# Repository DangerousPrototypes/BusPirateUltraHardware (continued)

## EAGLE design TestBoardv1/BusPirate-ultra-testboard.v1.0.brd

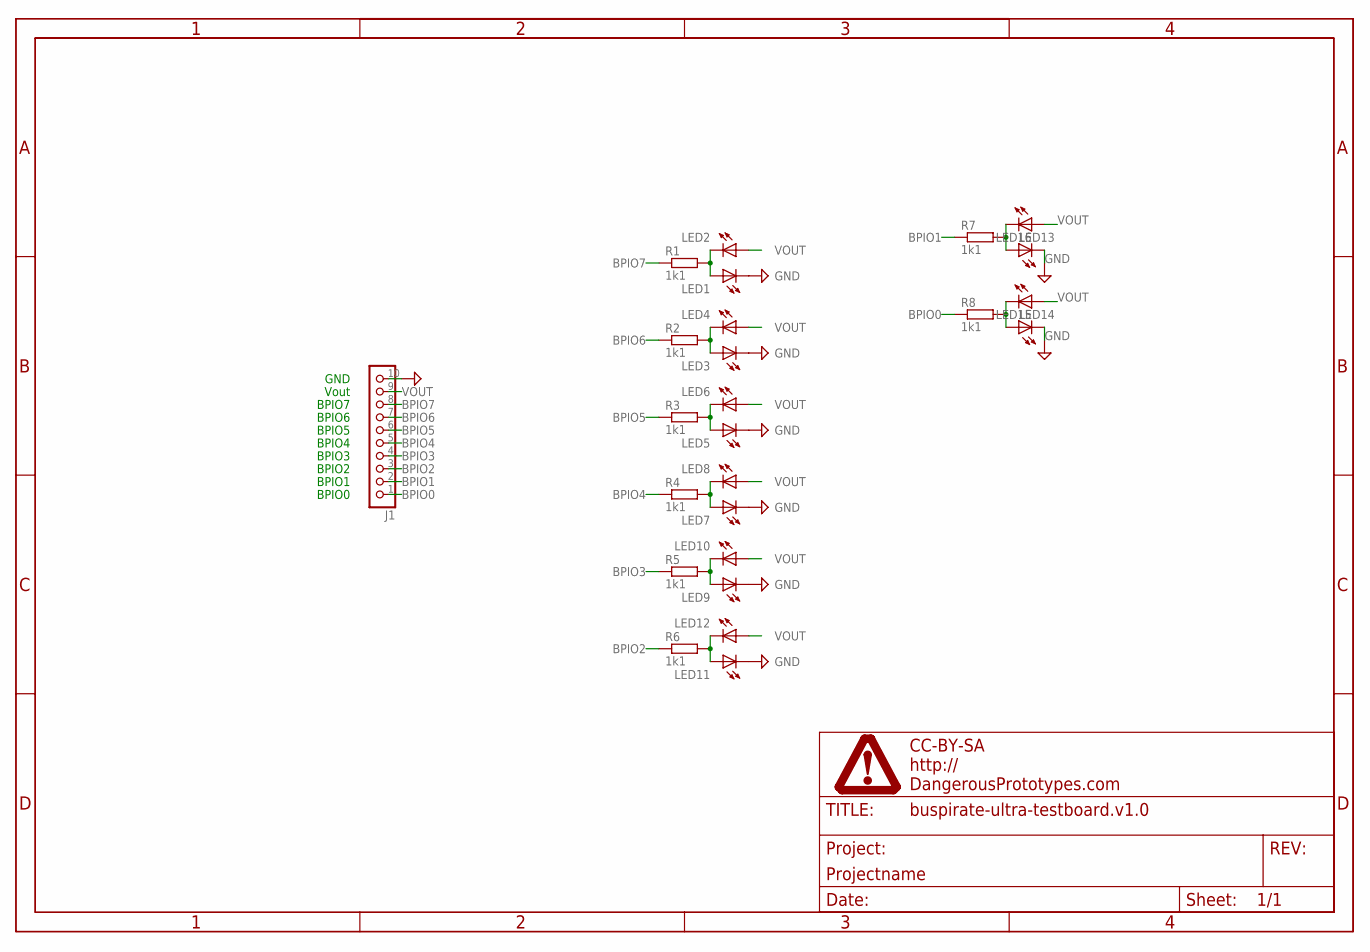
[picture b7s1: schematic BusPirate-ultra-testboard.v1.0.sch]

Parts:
J1: CON_HEADER_1X10-RIGHT_ANGLED_PTH; M1X10_FEMALE_RIGHT_ANGLED_PTH
LED1, LED2, LED3, LED4, LED5, LED6, LED7, LED8, LED9, LED10, LED11, LED12, LED13, LED14, LED15, LED16: LED-0805; LED-805
PAGE1: FRAME_DINA4_L; DP_LOGO
R1, R2, R3, R4, R5, R6, R7, R8: 1k1; R603

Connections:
BPIO0: J1.1, R8.1
BPIO1: J1.2, R7.1
BPIO2: J1.3, R6.1
BPIO3: J1.4, R5.1
BPIO4: J1.5, R4.1
BPIO5: J1.6, R3.1
BPIO6: J1.7, R2.1
BPIO7: J1.8, R1.1
GND: J1.10, LED1.C, LED3.C, LED5.C, LED7.C, LED9.C, LED11.C, LED13.C, LED14.C
unnamed: LED1.A, LED2.C, R1.2
unnamed: LED3.A, LED4.C, R2.2
unnamed: LED5.A, LED6.C, R3.2
unnamed: LED7.A, LED8.C, R4.2
unnamed: LED9.A, LED10.C, R5.2
unnamed: LED11.A, LED12.C, R6.2
unnamed: LED14.A, LED15.C, R8.2
unnamed: LED13.A, LED16.C, R7.2
VOUT: J1.9, LED2.A, LED4.A, LED6.A, LED8.A, LED10.A, LED12.A, LED15.A, LED16.A

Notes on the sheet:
BPIO0
Vout
BPIO7
BPIO6
BPIO5
BPIO4
BPIO3
BPIO2
BPIO1
GND

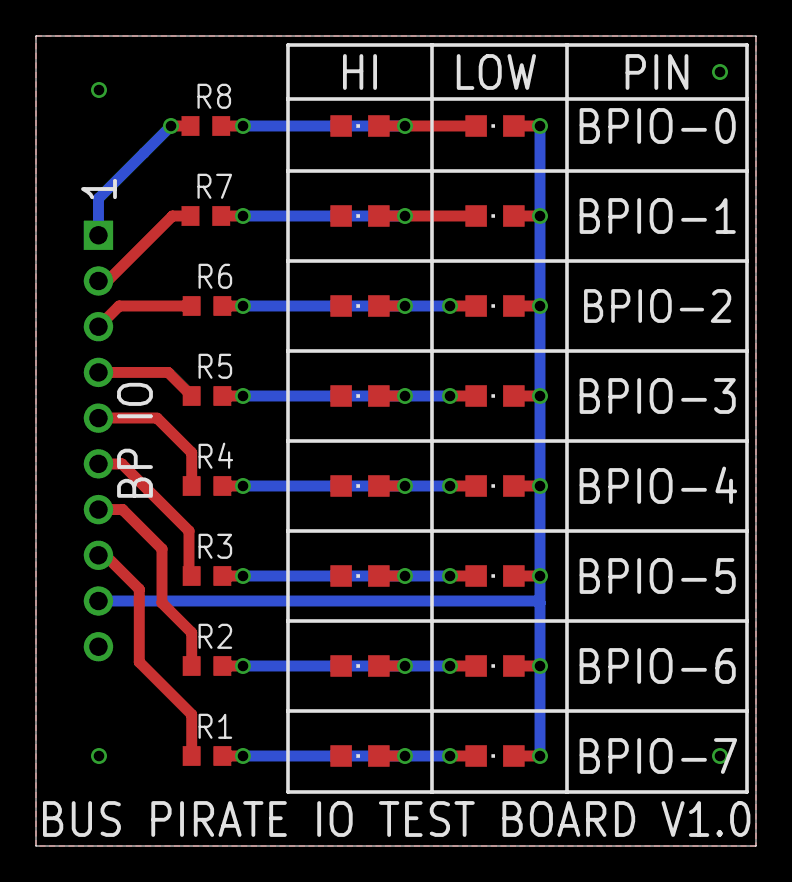
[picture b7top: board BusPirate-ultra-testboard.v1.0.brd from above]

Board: 2 copper layers, 40.0 x 45.0 mm, 26 parts (1 on the bottom side), 18 nets.

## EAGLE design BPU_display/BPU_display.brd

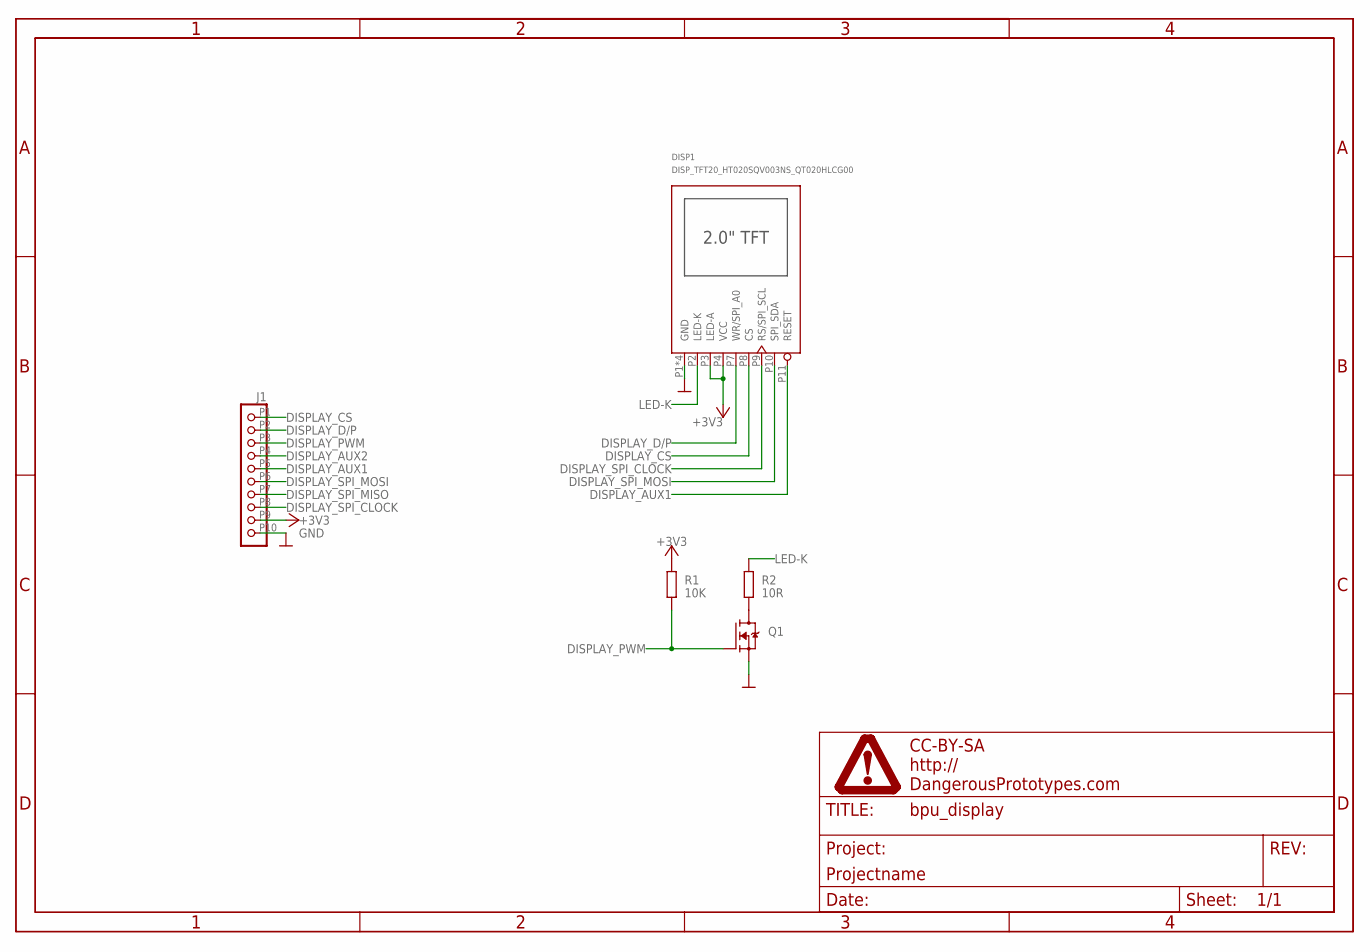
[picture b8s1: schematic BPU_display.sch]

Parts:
DISP1: DISP_TFT20_HT020SQV003NS_QT020HLCG00; HT020SQV003NS_QT020HLCG00
J1: CON_MOLEX_MALE_SMT_RIGHT_ANGLE_1.25; MOLEX_532611071
PAGE1: FRAME_DINA4_L; DP_LOGO
Q1: TRANSISTOR_FET_BS170-SOT-23; SOT-23
R1: 10K; R0603
R2: 10R; R0603

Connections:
+3V3: DISP1.P3 (LED-A), DISP1.P4 (VCC), J1.P9 (9), R1.2
DISPLAY_AUX1: DISP1.P11 (RESET), J1.P5 (5)
DISPLAY_AUX2: J1.P4 (4)
DISPLAY_CS: DISP1.P8 (CS), J1.P1 (1)
DISPLAY_D/P: DISP1.P7 (WR/SPI_A0), J1.P2 (2)
DISPLAY_PWM: J1.P3 (3), Q1.1 (G), R1.1
DISPLAY_SPI_CLOCK: DISP1.P9 (RS/SPI_SCL), J1.P8 (8)
DISPLAY_SPI_MISO: J1.P7 (7)
DISPLAY_SPI_MOSI: DISP1.P10 (SPI_SDA), J1.P6 (6)
GND: DISP1.P1 (GND), DISP1.P5 (GND), DISP1.P6 (GND), DISP1.P12 (GND), J1.P10 (10), Q1.2 (S)
LED-K: DISP1.P2 (LED-K), R2.2
unnamed: Q1.3 (D), R2.1

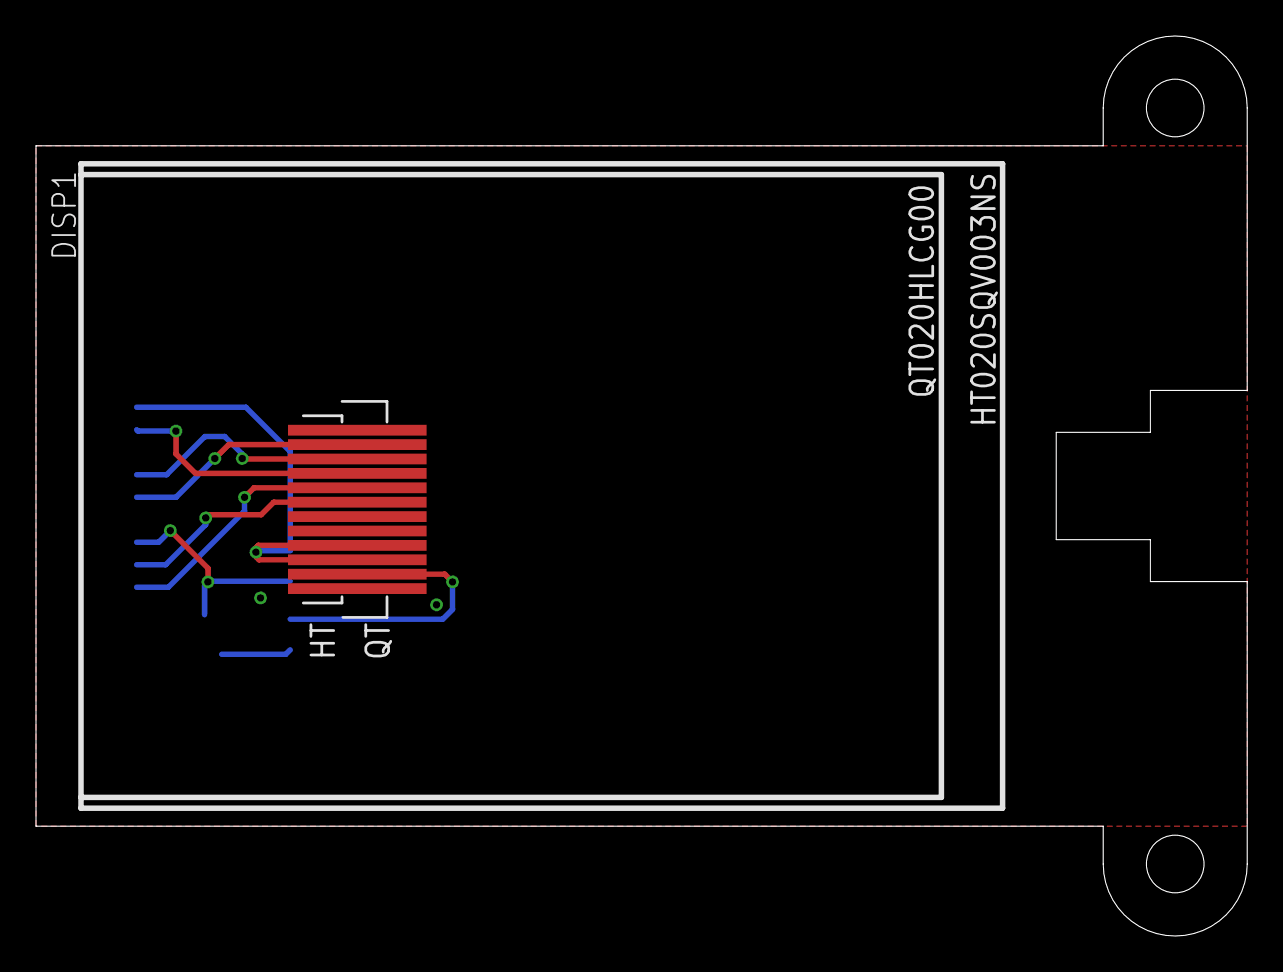
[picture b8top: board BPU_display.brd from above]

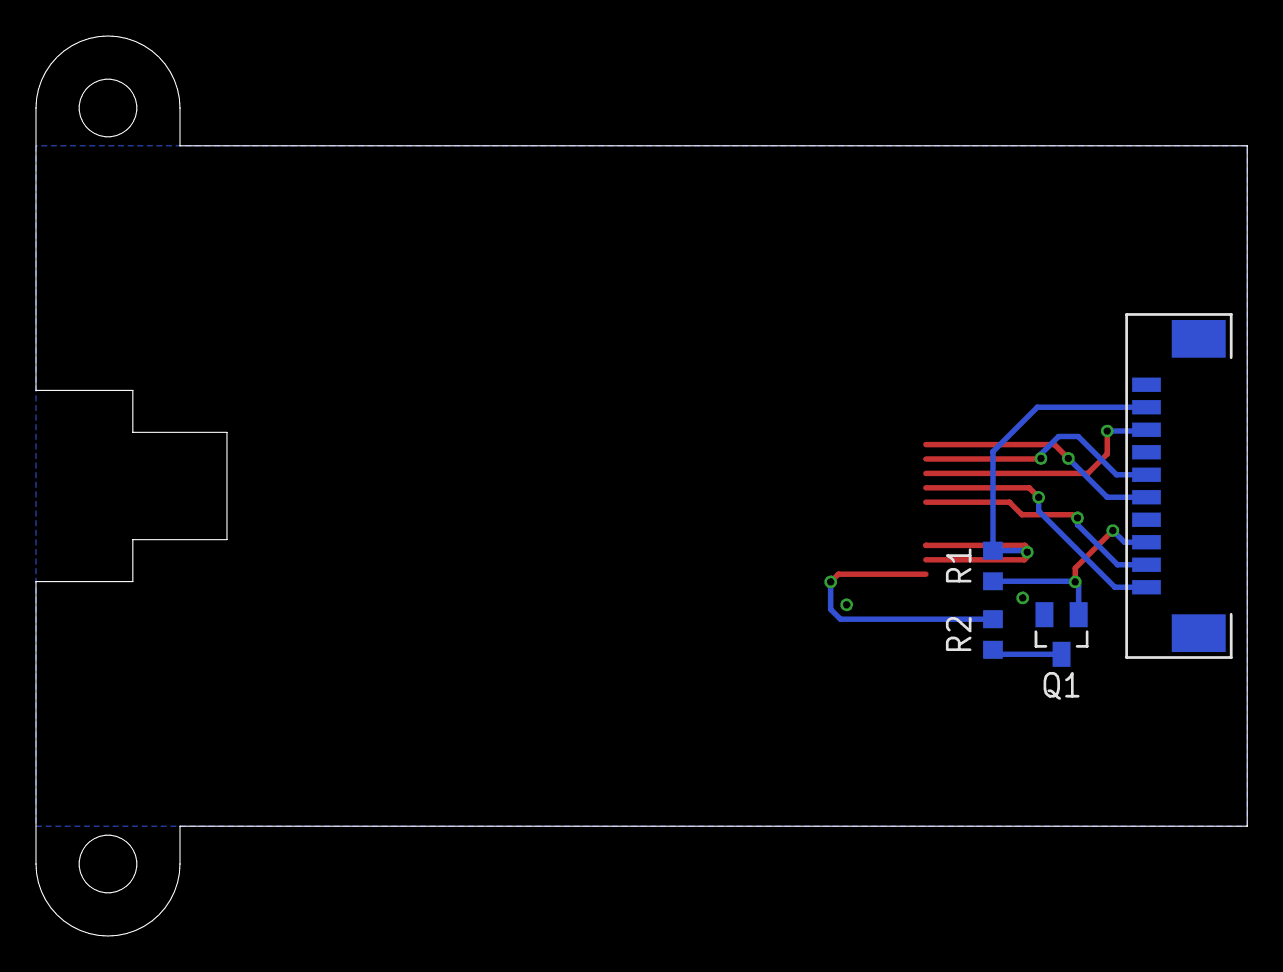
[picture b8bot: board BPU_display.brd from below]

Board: 2 copper layers, 67.3 x 50.0 mm, 6 parts (4 on the bottom side), 10 nets.

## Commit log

2019-08-26 initial check in from old repo https://github.com/DangerousPrototypes/Bus_Pirate_Ultra
2019-08-26 spreadsheets for calculating margining on the Vreg
2019-08-28 continue routing
2019-08-28 routed power traces
2019-08-29 board routing done, add usbc bottom PTH chassis mount library
2019-08-30 creted gerber for v1b
2019-09-06 added BP 'sail' daughter board
2019-09-06 make IO connector protrusion clearance to 1.5mm
2019-09-06 add DWG reference
2019-09-10 added vout and GND test point. add LED status to vout
2019-09-10 created geber for BPU display
2019-09-11 fix testboard IO header to match v1b, created gerbers
2019-09-24 new BPUltra.v.1.0C revision broke RN3 to individual 10K R603 resistors Added 1uF 0603 cap to U14 connect OE and DIR of latch (245) to FPGA Change values of the following parts: R27 to 100K R32 to 10K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
2019-10-03 fix bom parts naming change back to original SC-70-5 and SC-70-6 footprints for 74LVC1G07DBV and SN74LVC1T45DBV added decoupling caps for open drain buffers(on going)
2019-10-04 Revert previous commit to v1b, wrong version commited. changes should be on v1c not v1b.
    This reverts commit d10a26b079303959180bb4ab2616075854f9b9d1.
2019-10-05 new BPUltra.v.1.0C revision removed some text labels renamed BPIO pin labels fix bom parts naming change back to original SC-70-5 and SC-70-6 footprints for 74LVC1G07DBV and SN74LVC1T45DBV added deco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
2019-10-05 re-number parts logically changed C302 to 1uF add 4.7uF input cap on VR1 add 4.7uF input cap on VR2 add RC filter 25R and 1.5nF on ADC MUX buffer
2019-10-10 added ADC ADS7041 and wired to FPGA pin 45, 47 and 48 changed 3.3V regulator to bigger MCP1700 changed mux to 16-bit version 74HCT4067, added one new address line S3 to FPGA (not connected yet) conne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
2019-10-10 change supply of ADC chip to 3.3V
2019-10-15 updates on v1c schematic moved MCU_VPU to PA9, free up A10 moved DISPLAY_CS to PF11 (former DISPLAY_D/P) and DISPLAY_D/P to PB1, free up A6 moved FPGA MCU_INT1 from GBIN5 to FPGA pin 115 wired PG8 to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
2019-10-15 renamed DISPLAY_AUX2 to DISPLAY_AUX1 connected to PB1 renamed DISPLAY_AUX1 to DISPLAY_RESET and connected to PB2/BOOT1, wired a pull down resistor too rewired DISPLAY_CS from PF11 to PC4 rewired DISP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
2019-10-15 rewiring of v1c schematic continues
    renamed MCU_AUX7 to MCU_INT0
    renamed MCU_AUX8 to MCU_INT1
    renamed MCU_INT0 to MCU_PWM0
    renamed PWM to MCU_PWM1
    moved LAT_OE to FPGA pin 96
    moved LAT_DIR to FPGA pin 95
2019-10-16 continued on v1c schematic changes renamed MCU_AUX4 to MCU_INT3 and move it from MCU PD6 to PD2 renamed MCU_INT1I to MCU_AUX0 fix display connections
2019-10-16 continue on v1c schematic revisions -removed net DISPLAY_CSI on MCU pin 49 -renamed MCU_AUX5 to MCU_AUX4 and MCU_AUX6 to MCU_AUX5 -renamed MCU_ADC5 to MCU_ADC2 -renamed MCU_ADC6 to MCU_ADC3 -wired MC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
2019-10-20 finishing up routing on v1c board
2019-10-22 change display connector to FPC connector, done routing
2019-11-02 update reference dwg
2019-12-14 display board, fonts, 25lc eeprom breakout test board
2019-12-14 display board reorganization.
2020-04-21 preliminary commit of Bus Pirate Ultra v2, additional designs attribute to ULX3s https://github.com/emard/ulx3s and Butterstick https://github.com/gregdavill/ButterStick
2020-06-01 added 3d model of bus pirate ultra v1 case in freecad
2021-04-13 Added boxy corner version of the case on v1.1
2021-04-14 added v1.2 case, revert usb port back to rounded corner hole
